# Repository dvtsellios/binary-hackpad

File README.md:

# binary-hackpad

This is a hackpad that types in binary, so 1s and 0s. It also has a space button, a delete button and an enter button.

I built this in order to make typing a living nightmare basically. It uses the hackpad kit. The case is 3d printed and the pcb will be made through pcb way

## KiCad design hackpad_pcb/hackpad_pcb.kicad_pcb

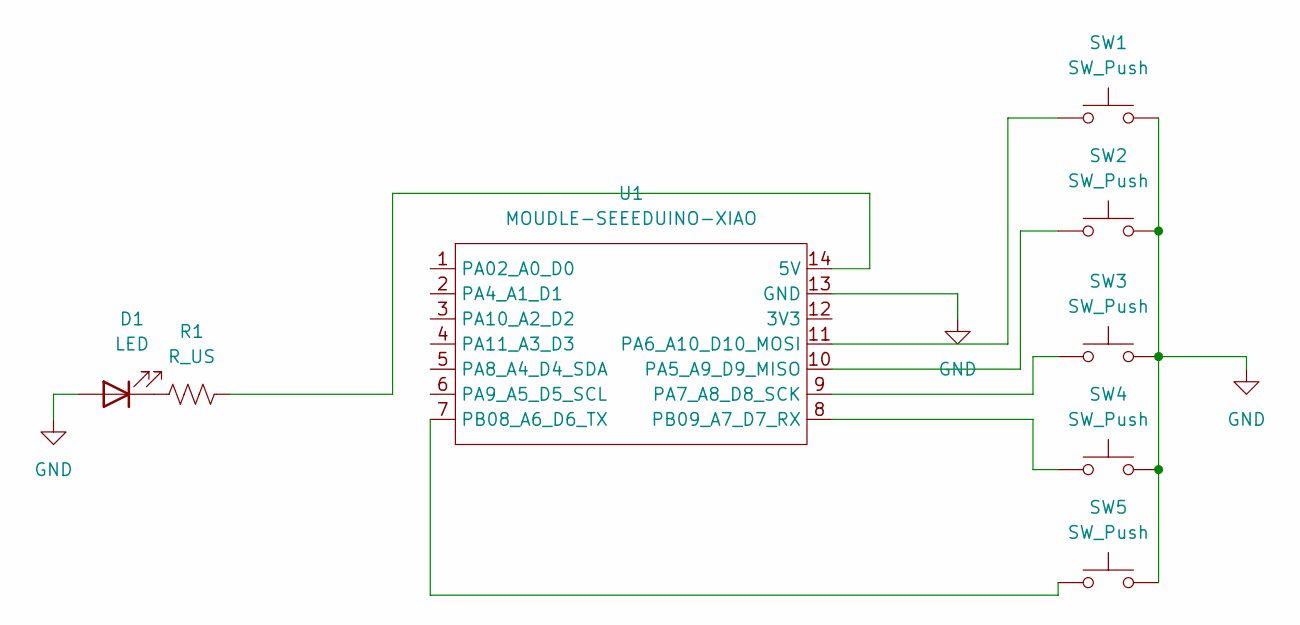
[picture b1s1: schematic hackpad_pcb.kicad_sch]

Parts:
D1: LED; LED_D3.0mm
R1: R_US; R_Axial_DIN0207_L6.3mm_D2.5mm_P10.16mm_Horizontal
SW1, SW2, SW3, SW4, SW5: SW_Push; SW_Cherry_MX_1.00u_PCB
U1: MOUDLE-SEEEDUINO-XIAO; XIAO-Generic-Hybrid-14P-2.54-21X17.8MM

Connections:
GND: D1.2 (A), SW1.2, SW2.2, SW3.2, SW4.2, SW5.2, U1.13 (GND)
unnamed: D1.1 (K), R1.2
unnamed: R1.1, U1.14 (5V)
unnamed: SW2.1, U1.10 (PA5_A9_D9_MISO)
unnamed: SW1.1, U1.11 (PA6_A10_D10_MOSI)
unnamed: SW3.1, U1.9 (PA7_A8_D8_SCK)
unnamed: SW5.1, U1.7 (PB08_A6_D6_TX)
unnamed: SW4.1, U1.8 (PB09_A7_D7_RX)

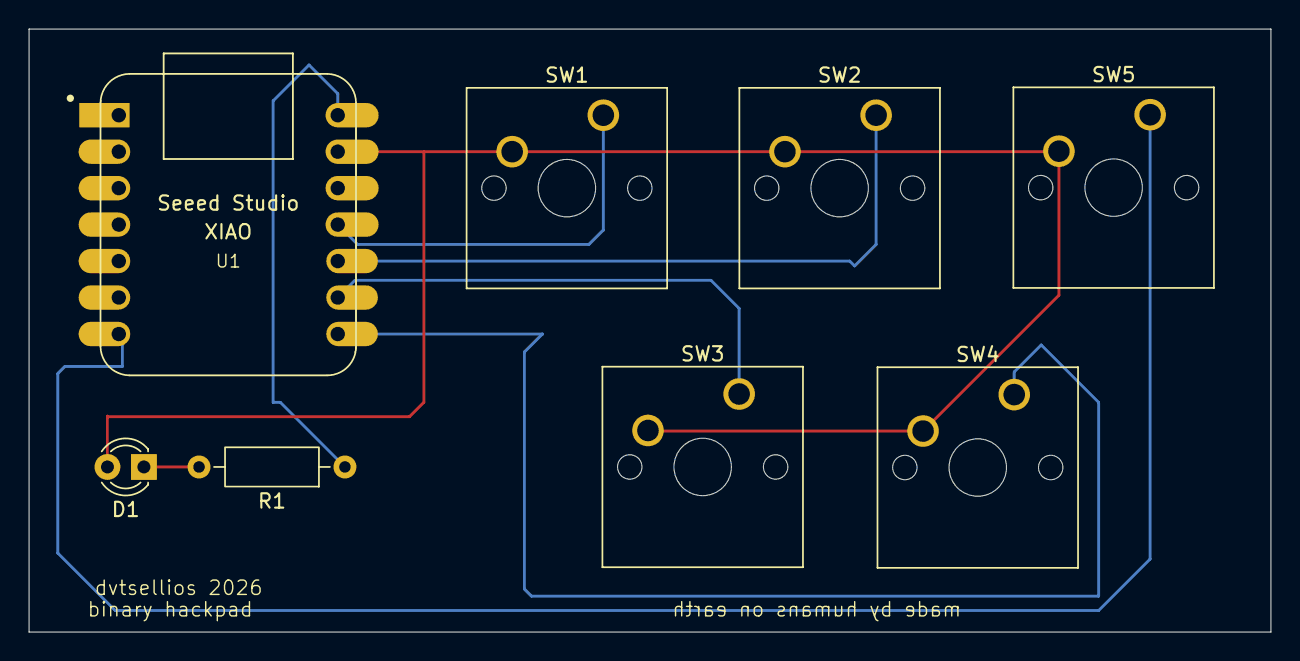
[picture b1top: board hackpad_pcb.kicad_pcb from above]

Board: 2 copper layers, 86.5 x 42.0 mm, 8 parts (0 on the bottom side), 8 nets.
